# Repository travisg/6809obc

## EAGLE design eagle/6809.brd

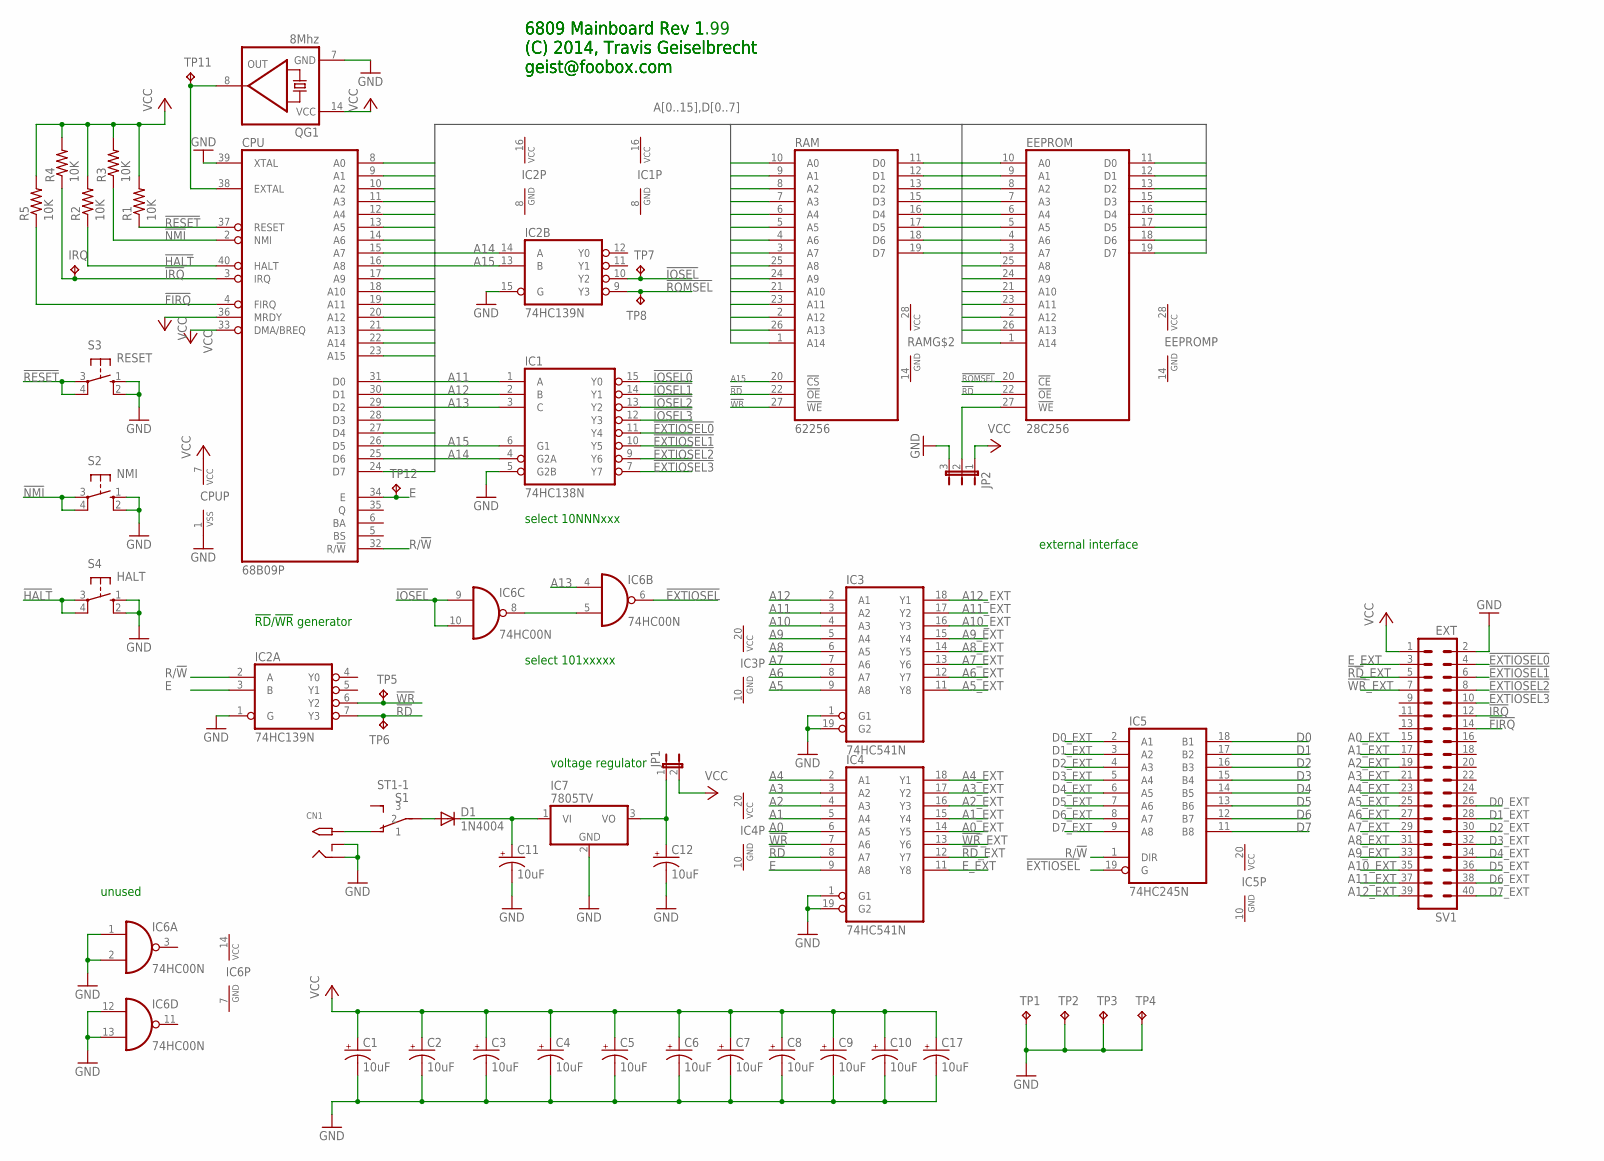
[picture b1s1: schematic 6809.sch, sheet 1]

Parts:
C1, C2, C3, C4, C5, C6, C7, C8, C9, C10, C11, C12, C17: 10uF; E1,8-4
CN1: 2.1MMJACKTHM; PJ-102A
CPU: 68B09P; DIL40
D1: 1N4004; DO41-10
EEPROM: 28C256; DIL28
IC1: 74HC138N; DIL16
IC2: 74HC139N; DIL16
IC3, IC4: 74HC541N; DIL20
IC5: 74HC245N; DIL20
IC6: 74HC00N; DIL14
IC7: 7805TV; TO220V
IRQ: TPTP10R; TP10R
JP1: JP1E; JP1
JP2: JP2E; JP2
QG1: 8Mhz; DIL14S
R1, R2, R3, R4, R5: 10K; 0207/10
RAM: 62256; DIL28
S1: ST1-1
S2: NMI; B3F-10XX
S3: RESET; B3F-10XX
S4: HALT; B3F-10XX
SV1: EXT; MA20-2
TP1, TP2, TP3, TP4: TPPAD1-13; P1-13
TP5, TP6, TP7, TP8, TP11, TP12: TPTP10R; TP10R

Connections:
!EXTIOSEL: IC5.19 (G), IC6.6 (O)
!EXTIOSEL0: IC1.11 (Y4), SV1.4
!EXTIOSEL1: IC1.10 (Y5), SV1.6
!EXTIOSEL2: IC1.9 (Y6), SV1.8
!EXTIOSEL3: IC1.7 (Y7), SV1.10
!FIRQ: CPU.4 (FIRQ), R5.1, SV1.14
!HALT: CPU.40 (HALT), R2.1, S4.3, S4.4 (P1)
!IOSEL: IC2.10 (Y2), IC6.9 (I0), IC6.10 (I1), TP7.TP
!IOSEL0: IC1.15 (Y0); also elsewhere on the board
!IOSEL1: IC1.14 (Y1)
!IOSEL2: IC1.13 (Y2)
!IOSEL3: IC1.12 (Y3)
!IRQ: CPU.3 (IRQ), IRQ.TP, R4.1, SV1.12; also elsewhere on the board
!NMI: CPU.2 (NMI), R3.1, S2.3, S2.4 (P1)
!RD: EEPROM.22 (!OE), IC2.7 (Y3), IC4.8 (A7), RAM.22 (!OE), TP6.TP; also elsewhere on the board
!RD!_EXT: IC4.12 (Y7), SV1.5
!RESET: CPU.37 (RESET), R1.1, S3.3, S3.4 (P1)
!ROMSEL: EEPROM.20 (!CE), IC2.9 (Y3), TP8.TP
!WR: IC2.6 (Y2), IC4.7 (A6), RAM.27 (!WE), TP5.TP; also elsewhere on the board
!WR!_EXT: IC4.13 (Y6), SV1.7
A0: CPU.8 (A0), EEPROM.10 (A0), IC4.6 (A5), RAM.10 (A0); also elsewhere on the board
A0_EXT: IC4.14 (Y5), SV1.15
A1: CPU.9 (A1), EEPROM.9 (A1), IC4.5 (A4), RAM.9 (A1); also elsewhere on the board
A1_EXT: IC4.15 (Y4), SV1.17
A2: CPU.10 (A2), EEPROM.8 (A2), IC4.4 (A3), RAM.8 (A2); also elsewhere on the board
A2_EXT: IC4.16 (Y3), SV1.19
A3: CPU.11 (A3), EEPROM.7 (A3), IC4.3 (A2), RAM.7 (A3)
A3_EXT: IC4.17 (Y2), SV1.21
A4: CPU.12 (A4), EEPROM.6 (A4), IC4.2 (A1), RAM.6 (A4)
A4_EXT: IC4.18 (Y1), SV1.23
A5: CPU.13 (A5), EEPROM.5 (A5), IC3.9 (A8), RAM.5 (A5)
A5_EXT: IC3.11 (Y8), SV1.25
A6: CPU.14 (A6), EEPROM.4 (A6), IC3.8 (A7), RAM.4 (A6)
A6_EXT: IC3.12 (Y7), SV1.27
A7: CPU.15 (A7), EEPROM.3 (A7), IC3.7 (A6), RAM.3 (A7)
A7_EXT: IC3.13 (Y6), SV1.29
A8: CPU.16 (A8), EEPROM.25 (A8), IC3.6 (A5), RAM.25 (A8)
A8_EXT: IC3.14 (Y5), SV1.31
A9: CPU.17 (A9), EEPROM.24 (A9), IC3.5 (A4), RAM.24 (A9)
A9_EXT: IC3.15 (Y4), SV1.33
A10: CPU.18 (A10), EEPROM.21 (A10), IC3.4 (A3), RAM.21 (A10)
A10_EXT: IC3.16 (Y3), SV1.35
A11: CPU.19 (A11), EEPROM.23 (A11), IC1.1 (A), IC3.3 (A2), RAM.23 (A11)
A11_EXT: IC3.17 (Y2), SV1.37
A12: CPU.20 (A12), EEPROM.2 (A12), IC1.2 (B), IC3.2 (A1), RAM.2 (A12)
A12_EXT: IC3.18 (Y1), SV1.39
A13: CPU.21 (A13), EEPROM.26 (A13), IC1.3 (C), IC6.4 (I0), RAM.26 (A13)
A14: CPU.22 (A14), EEPROM.1 (A14), IC1.4 (G2A), IC2.14 (A), RAM.1 (A14)
A15: CPU.23 (A15), IC1.6 (G1), IC2.13 (B), RAM.20 (!CS)
D0: CPU.31 (D0), EEPROM.11 (D0), IC5.18 (B1), RAM.11 (D0); also elsewhere on the board
D0_EXT: IC5.2 (A1), SV1.26
D1: CPU.30 (D1), EEPROM.12 (D1), IC5.17 (B2), RAM.12 (D1); also elsewhere on the board
D1_EXT: IC5.3 (A2), SV1.28
D2: CPU.29 (D2), EEPROM.13 (D2), IC5.16 (B3), RAM.13 (D2); also elsewhere on the board
D2_EXT: IC5.4 (A3), SV1.30
D3: CPU.28 (D3), EEPROM.15 (D3), IC5.15 (B4), RAM.15 (D3); also elsewhere on the board
D3_EXT: IC5.5 (A4), SV1.32
D4: CPU.27 (D4), EEPROM.16 (D4), IC5.14 (B5), RAM.16 (D4); also elsewhere on the board
D4_EXT: IC5.6 (A5), SV1.34
D5: CPU.26 (D5), EEPROM.17 (D5), IC5.13 (B6), RAM.17 (D5); also elsewhere on the board
D5_EXT: IC5.7 (A6), SV1.36
D6: CPU.25 (D6), EEPROM.18 (D6), IC5.12 (B7), RAM.18 (D6); also elsewhere on the board
D6_EXT: IC5.8 (A7), SV1.38
D7: CPU.24 (D7), EEPROM.19 (D7), IC5.11 (B8), RAM.19 (D7); also elsewhere on the board
D7_EXT: IC5.9 (A8), SV1.40
E: CPU.34 (E), IC2.3 (B), IC4.9 (A8), TP12.TP
E_EXT: IC4.11 (Y8), SV1.3
GND: C1.-, C2.-, C3.-, C4.-, C5.-, C6.-, C7.-, C8.-, C9.-, C10.-, C11.-, C12.-, C17.-, CN1.RING, CN1.RING_SW, CPU.1 (VSS), CPU.39 (XTAL), EEPROM.14 (GND), IC1.5 (G2B), IC1.8 (GND), IC2.1 (G), IC2.8 (GND), IC2.15 (G), IC3.1 (G1), IC3.10 (GND), IC3.19 (G2), IC4.1 (G1), IC4.10 (GND), IC4.19 (G2), IC5.10 (GND), IC6.1 (I0), IC6.2 (I1), IC6.7 (GND), IC6.12 (I0), IC6.13 (I1), IC7.2 (GND), JP2.3, QG1.7 (GND), RAM.14 (GND), S2.1 (S), S2.2 (S1), S3.1 (S), S3.2 (S1), S4.1 (S), S4.2 (S1), SV1.2, TP1.TP, TP2.TP, TP3.TP, TP4.TP; also elsewhere on the board
unnamed: C11.+, D1.C, IC7.1 (VI)
unnamed: IC6.5 (I1), IC6.8 (O)
unnamed: CN1.TIP, S1.P$1 (1)
unnamed: CPU.38 (EXTAL), QG1.8 (OUT), TP11.TP
unnamed: D1.A, S1.P$2 (2)
unnamed: EEPROM.27 (!WE), JP2.2
unnamed: C12.+, IC7.3 (VO), JP1.1
R/!W: CPU.32 (R/!W), IC2.2 (A), IC5.1 (DIR)
VCC: C1.+, C2.+, C3.+, C4.+, C5.+, C6.+, C7.+, C8.+, C9.+, C10.+, C17.+, CPU.7 (VCC), CPU.33 (DMA/BREQ), CPU.36 (MRDY), EEPROM.28 (VCC), IC1.16 (VCC), IC2.16 (VCC), IC3.20 (VCC), IC4.20 (VCC), IC5.20 (VCC), IC6.14 (VCC), JP1.2, JP2.1, QG1.14 (VCC), R1.2, R2.2, R3.2, R4.2, R5.2, RAM.28 (VCC), SV1.1; also elsewhere on the board

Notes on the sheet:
!RD!/!WR! generator
external interface
select 10NNNxxx
select 101xxxxx
voltage regulator
unused
6809 Mainboard Rev 1.99 (C) 2014, Travis Geiselbrecht geist@foobox.com
6809 Mainboard Rev 1 (C) 2014, Travis Geiselbrecht geist@foobox.com

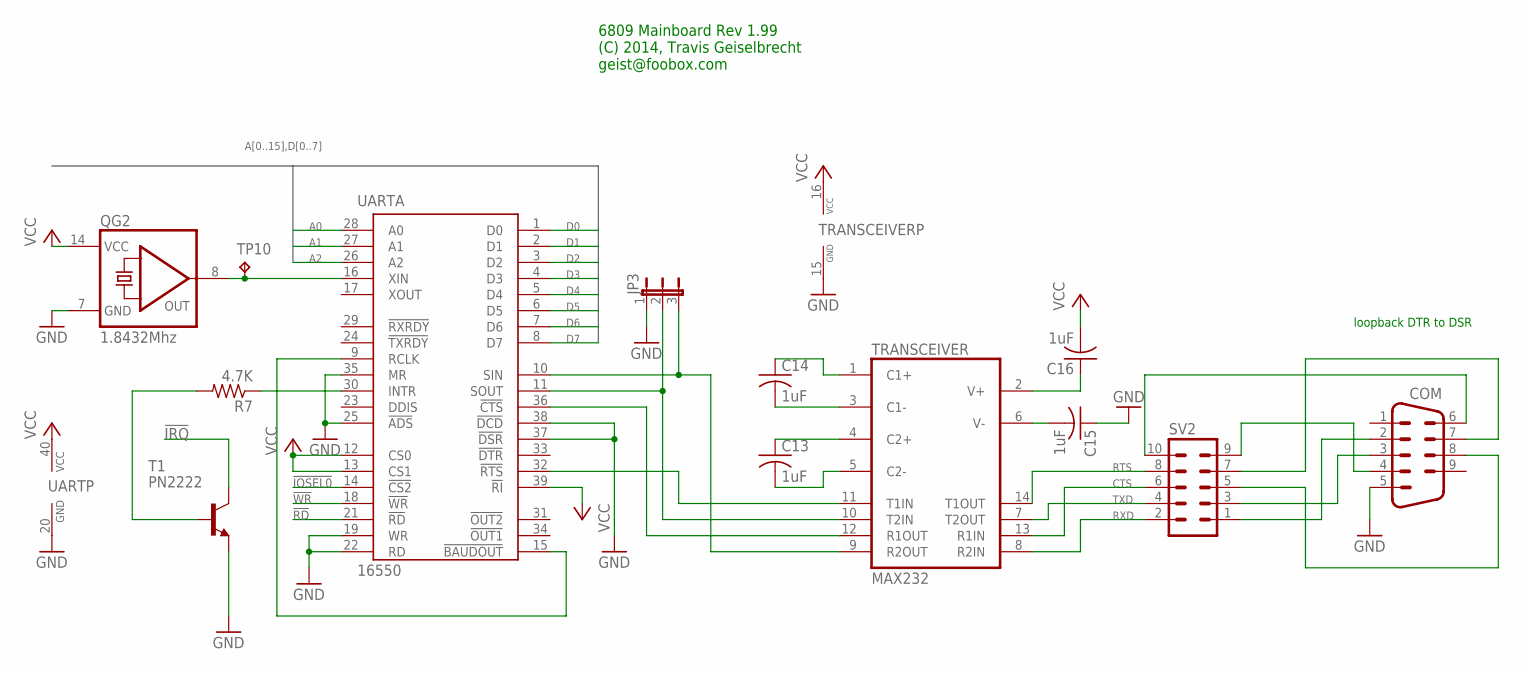
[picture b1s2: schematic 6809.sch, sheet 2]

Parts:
C13, C14, C15, C16: 1uF; C025-025X050
COM: M09HP
JP3: JP2E; JP2
QG2: 1.8432Mhz; DIL14S
R7: 4.7K; 0207/10
SV2: MA05-2
T1: PN2222; TO92-EBC-OVAL
TP10: TPTP10R; TP10R
TRANSCEIVER: MAX232; DIL16
UART: 16550; DIL40

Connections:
!IOSEL0: UART.14 (!CS2); also elsewhere on the board
!IRQ: T1.C; also elsewhere on the board
!RD: UART.21 (!RD); also elsewhere on the board
!WR: UART.18 (!WR); also elsewhere on the board
A0: UART.28 (A0); also elsewhere on the board
A1: UART.27 (A1); also elsewhere on the board
A2: UART.26 (A2); also elsewhere on the board
CTS: SV2.6, TRANSCEIVER.13 (R1IN)
D0: UART.1 (D0); also elsewhere on the board
D1: UART.2 (D1); also elsewhere on the board
D2: UART.3 (D2); also elsewhere on the board
D3: UART.4 (D3); also elsewhere on the board
D4: UART.5 (D4); also elsewhere on the board
D5: UART.6 (D5); also elsewhere on the board
D6: UART.7 (D6); also elsewhere on the board
D7: UART.8 (D7); also elsewhere on the board
GND: C15.1, COM.5, JP3.1, QG2.7 (GND), T1.E, TRANSCEIVER.15 (GND), UART.19 (WR), UART.20 (GND), UART.22 (RD), UART.25 (!ADS), UART.35 (MR), UART.37 (!DSR), UART.38 (!DCD); also elsewhere on the board
unnamed: QG2.8 (OUT), TP10.TP, UART.16 (XIN)
unnamed: TRANSCEIVER.11 (T1IN), UART.32 (!RTS)
unnamed: JP3.2, TRANSCEIVER.10 (T2IN), UART.11 (SOUT)
unnamed: TRANSCEIVER.12 (R1OUT), UART.36 (!CTS)
unnamed: COM.4, SV2.9
unnamed: C14.1, TRANSCEIVER.1 (C1+)
unnamed: C14.2, TRANSCEIVER.3 (C1-)
unnamed: JP3.3, TRANSCEIVER.9 (R2OUT), UART.10 (SIN)
unnamed: C13.1, TRANSCEIVER.4 (C2+)
unnamed: C13.2, TRANSCEIVER.5 (C2-)
unnamed: COM.2, SV2.1
unnamed: COM.8, SV2.5
unnamed: COM.7, SV2.7
unnamed: C16.1, TRANSCEIVER.2 (V+)
unnamed: COM.3, SV2.3
unnamed: C15.2, TRANSCEIVER.6 (V-)
unnamed: R7.2, T1.B
unnamed: R7.1, UART.30 (INTR)
unnamed: COM.6, SV2.10
unnamed: UART.9 (RCLK), UART.15 (!BAUDOUT)
RTS: SV2.8, TRANSCEIVER.14 (T1OUT)
RXD: SV2.2, TRANSCEIVER.8 (R2IN)
TXD: SV2.4, TRANSCEIVER.7 (T2OUT)
VCC: C16.2, QG2.14 (VCC), TRANSCEIVER.16 (VCC), UART.12 (CS0), UART.13 (CS1), UART.39 (!RI), UART.40 (VCC); also elsewhere on the board

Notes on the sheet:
loopback DTR to DSR
6809 Mainboard Rev 1.99 (C) 2014, Travis Geiselbrecht geist@foobox.com

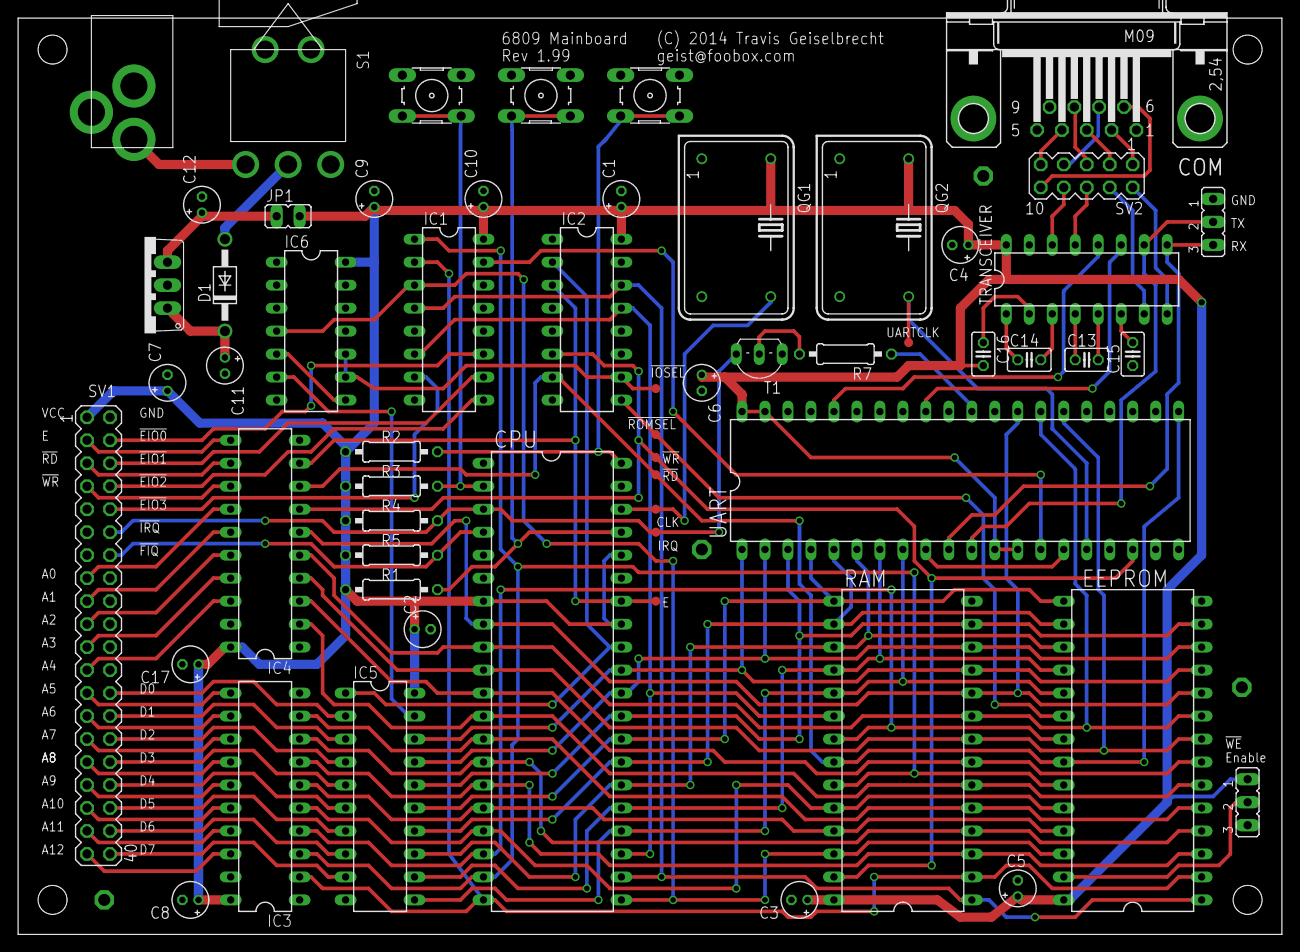
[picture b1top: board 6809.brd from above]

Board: 2 copper layers, 139.7 x 101.3 mm, 62 parts (0 on the bottom side), 98 nets.

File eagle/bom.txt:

Partlist exported from /home/geist/eagle/6809/6809.sch at 7/14/14 10:38 PM

Qty Value        Device          Package       Parts                                                  Description                                                                              
1                JP1E            JP1           JP1                                                    JUMPER                                                                                   
1                JP2E            JP2           JP2                                                    JUMPER                                                                                   
1                MA04-2          MA04-2        SV2                                                    PIN HEADER                                                                               
1   1.8432Mhz    QG5860          DIL14S        QG2                                                    CRYSTAL RESONATOR                                                                        
5   10K          R-US_0207/10    0207/10       R1, R2, R3, R4, R5                                     RESISTOR, American symbol                                                                
13  10uF         CPOL-USE1.8-4   E1,8-4        C1, C2, C3, C4, C5, C6, C7, C8, C9, C10, C11, C12, C17 POLARIZED CAPACITOR, American symbol                                                     
1   16550        16550           DIL40         UART                                                                                                                                            
1   1N4004       1N4004          DO41-10       D1                                                     DIODE                                                                                    
4   1uF          C-US025-025X050 C025-025X050  C13, C14, C15, C16                                     CAPACITOR, American symbol                                                               
1   2.1MMJACKTHM 2.1MMJACKTHM    PJ-102A       CN1                                                    2.1mm x 5.5mm THM DC jack with internal switch. Digikey part #PJ-102A, 4UCON part #05537 
1   28C256       28C256          DIL28         EEPROM                                                 8K x 8 EEPROM                                                                            
1   4.7K         R-US_0207/10    0207/10       R7                                                     RESISTOR, American symbol                                                                
1   62256        62256           DIL28         RAM                                                    32KB sram                                                                                
1   68B09P       6809            DIL40         CPU                                                    MICROCONTROLLER/MEMORY DEVICE                                                            
1   74HC00N      74HC00N         DIL14         IC6                                                    Quad 2-input NAND gate                                                                   
1   74HC138N     74HC138N        DIL16         IC1                                                    3-line to 8-line DECODER/DEMULTIPLEXER                                                   
1   74HC139N     74HC139N        DIL16         IC2                                                    Dual 2-line to 4-line DECODER/DEMULTIPLEXER                                              
1   74HC245N     74HC245N        DIL20         IC5                                                    Octal BUS TRANSCEIVER, 3-state                                                           
2   74HC541N     74HC541N        DIL20         IC3, IC4                                               Octal BUFFER and LINE DRIVER, 3-state                                                    
1   7805TV       7805TV          TO220V        IC7                                                    Positive VOLTAGE REGULATOR                                                               
1   8Mhz         QG5860          DIL14S        QG1                                                    CRYSTAL RESONATOR                                                                        
1   COM1         F09HP           F09HP         DE9                                                    SUB-D                                                                                    
1   EXT          MA20-2          MA20-2        SV1                                                    PIN HEADER                                                                               
1   HALT         10-XX           B3F-10XX      S4                                                     OMRON SWITCH                                                                             
1   MAX232       MAX232          DIL16         TRANSCEIVER                                            RS232 TRANSCEIVER                                                                        
1   NMI          10-XX           B3F-10XX      S2                                                     OMRON SWITCH                                                                             
1   PN2222       2N2222          TO92-EBC-OVAL T1                                                     NPN TRANSISTOR                                                                           
1   RESET        10-XX           B3F-10XX      S3                                                     OMRON SWITCH                                                                             
1   ST1-1        ST1-1           ST1-1         S1                                                                                                                                              
4   TPPAD1-13    TPPAD1-13       P1-13         TP1, TP2, TP3, TP4                                     Test pad                                                                                 
9   TPTP10R      TPTP10R         TP10R         RX, TP5, TP6, TP7, TP8, TP10, TP11, TP12, TX           Test pad

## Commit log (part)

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2014-07-19 revision 1 of the 6809 one board computer eagle cad files
2014-07-19 add license file for all of the contents of the repository
2014-07-19 [rom] initial checkin of some rom code
2014-07-23 [rom] add libihex submodule, build ihextobin, and use it to generate the bin file
2014-07-26 add .gitignore for eagle cad stuff
2016-10-28 [eagle] some work on a rev 2
2017-12-21 [rom] some rom tweakery
2017-12-21 [libihex] bump to newer version
2017-12-21 [rom][c] start to cobble together a C based rom
2017-12-21 WIP checkpoint C rom
2017-12-21 WIP monitor
2017-12-31 WIP move .S files to C, add compiler.h
2017-12-31 WIP compile as PIC
2017-12-31 WIP split things into more .c files
2017-12-31 WIP switch to monitor to using a tokenizer
